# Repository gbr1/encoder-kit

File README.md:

# encoder-kit
Erwhi Hedgehog encoders.<br>

<br>
<br>
***Copyright (c) 2019 Giovanni di Dio Bruno under MIT license.***

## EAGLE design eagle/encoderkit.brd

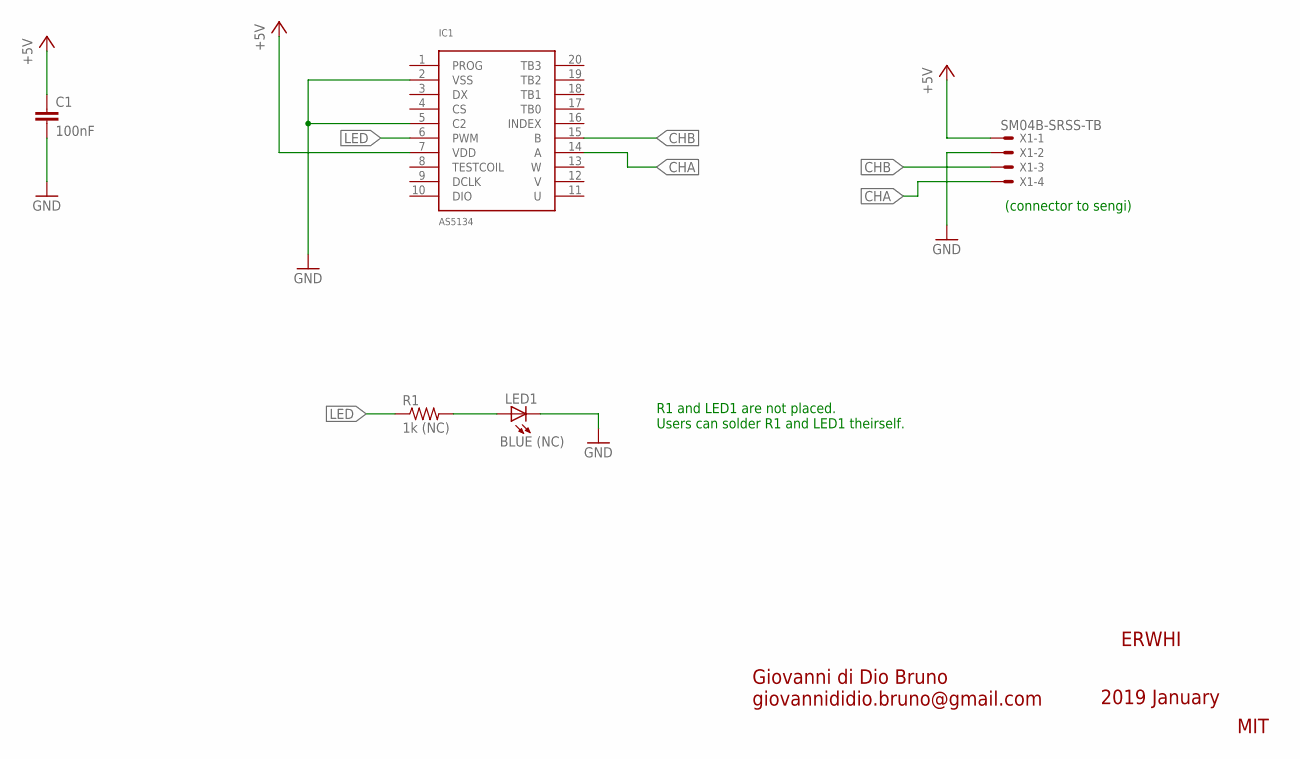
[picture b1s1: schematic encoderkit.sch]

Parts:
C1: 100nF; C0402
IC1: AS5134; SSOP20
LED1: BLUE (NC); CHIP-LED0603
R1: 1k (NC); R0402
X1: SM04B-SRSS-TB

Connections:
+5V: C1.1, IC1.7 (VDD), X1.1
CHA: IC1.14 (A), X1.4
CHB: IC1.15 (B), X1.3
GND: C1.2, IC1.2 (VSS), IC1.5 (C2), LED1.C, X1.2
LED: IC1.6 (PWM), R1.1
unnamed: LED1.A, R1.2

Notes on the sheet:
(connector to sengi)
Giovanni di Dio Bruno giovannididio.bruno@gmail.com
MIT
2019 January
ERWHI
R1 and LED1 are not placed. Users can solder R1 and LED1 theirself.

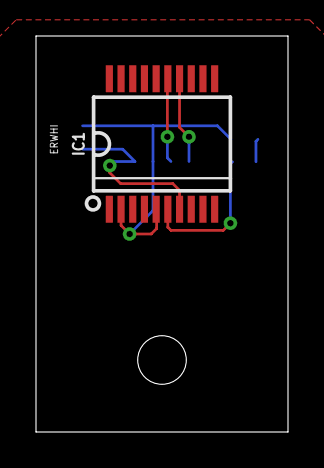
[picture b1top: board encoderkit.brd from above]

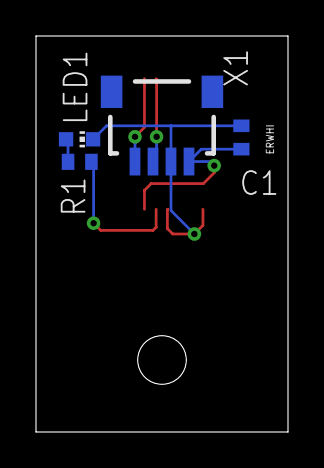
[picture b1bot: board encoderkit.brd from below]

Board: 2 copper layers, 14.0 x 22.0 mm, 5 parts (4 on the bottom side), 6 nets.
